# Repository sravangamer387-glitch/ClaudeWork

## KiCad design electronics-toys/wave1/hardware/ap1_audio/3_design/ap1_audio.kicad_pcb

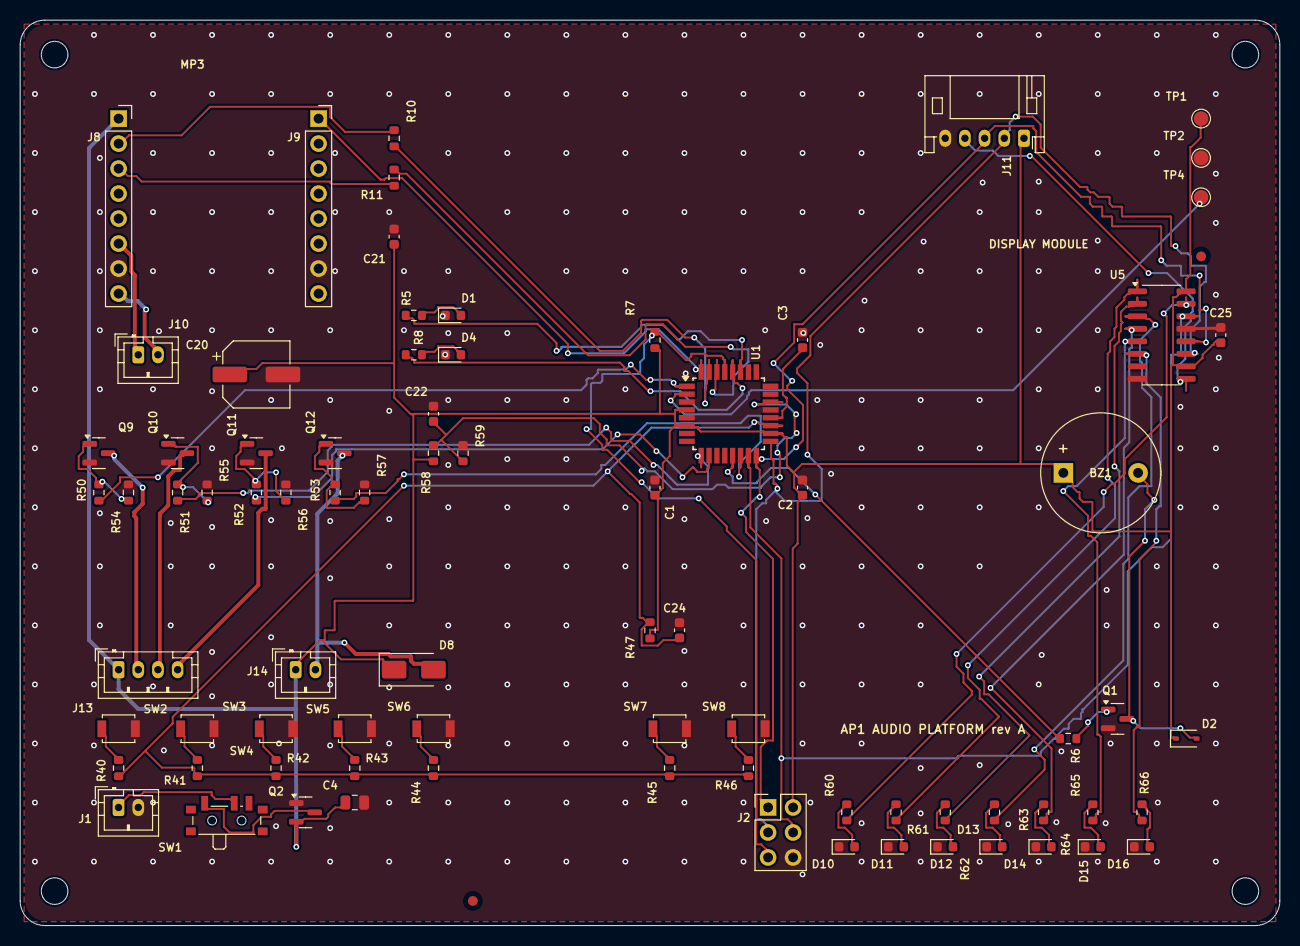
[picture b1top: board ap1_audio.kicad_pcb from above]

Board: 2 copper layers, 128.0 x 92.0 mm, 85 parts (0 on the bottom side), 60 nets.

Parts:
BZ1: Buzzer; Buzzer_12x9.5RM7.6
C1, C2, C3, C21, C22, C24, C25: 100n; C_0603_1608Metric
C4: 10u; C_0805_2012Metric
C20: 100u/35V; CP_Elec_6.3x7.7
D1: Green; LED_0603_1608Metric
D2: 1N4148WS; D_SOD-323
D4: Amber; LED_0603_1608Metric
D8: SS14; D_SMA
D10, D11, D12, D13, D14, D15, D16: Red; LED_0603_1608Metric
FID1, FID2: Fiducial; Fiducial_1mm_Mask2mm
H1, H2, H3, H4: M2.5; MountingHole_2.7mm_M2.5
J1: BATT 3xAA; JST_PH_B2B-PH-K_1x02_P2.00mm_Vertical
J2: ISP; PinHeader_2x03_P2.54mm_Vertical
J8: MP3 module left row (VCC RX TX DACR DACL SPK1 GND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; PinSocket_1x08_P2.54mm_Vertical
J9: MP3 module right row (BUSY .. GND IO1); PinSocket_1x08_P2.54mm_Vertical
J10: Speaker 3 W 4-8 ohm; JST_PH_B2B-PH-K_1x02_P2.00mm_Vertical
J11: Display module (VCC SCLK RCLK DIO GND); JST_PH_S5B-PH-K_1x05_P2.00mm_Horizontal
J13: RGB LED (common anode) / lamp; JST_PH_B4B-PH-K_1x04_P2.00mm_Vertical
J14: Projector motor; JST_PH_B2B-PH-K_1x02_P2.00mm_Vertical
Q1: MMBT3904; SOT-23
Q2: AO3401A; SOT-23
Q9, Q10, Q11, Q12: AO3400A; SOT-23
R5, R6, R8, R10, R11, R40, R60, R61, R62, R63, R64, R65, R66: 1k; R_0603_1608Metric
R7, R47: 10k; R_0603_1608Metric
R41: 2.2k; R_0603_1608Metric
R42: 3.9k; R_0603_1608Metric
R43: 6.8k; R_0603_1608Metric
R44: 12k; R_0603_1608Metric
R45: 22k; R_0603_1608Metric
R46: 47k; R_0603_1608Metric
R50, R51, R52, R53: 100; R_0603_1608Metric
R54, R55, R56, R57, R58, R59: 100k; R_0603_1608Metric
SW1: Power; SW_SPDT_PCM12
SW2: Button 1; SW_SPST_B3U-1000P
SW3: Button 2; SW_SPST_B3U-1000P
SW4: Button 3; SW_SPST_B3U-1000P
SW5: Button 4; SW_SPST_B3U-1000P
SW6: Button 5; SW_SPST_B3U-1000P
SW7: Button 6; SW_SPST_B3U-1000P
SW8: Button 7; SW_SPST_B3U-1000P
TP1, TP2, TP4: TP; TestPoint_Pad_D1.5mm
U1: ATmega328P-AU; TQFP-32_7x7mm_P0.8mm
U5: 74HC595; SOIC-16_3.9x9.9mm_P1.27mm

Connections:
+4V5: BZ1.1, C1.1, C2.1, C4.1, C20.1, C21.1, C25.1, D2.1, D8.1, J2.2, J8.1, J11.1, J13.1, J14.1, Q2.2, R7.1, R47.1, R58.1, TP1.1, U1.4, U1.6, U1.18, U5.10, U5.16
AREF: C3.1, U1.20
BAT_P: J1.1, SW1.2
BAT_SW: Q2.3, SW1.1
BTN0_N: R40.2, SW2.1
BTN1_N: R41.2, SW3.1
BTN2_N: R42.2, SW4.1
BTN3_N: R43.2, SW5.1
BTN4_N: R44.2, SW6.1
BTN5_N: R45.2, SW7.1
BTN6_N: R46.2, SW8.1
BTN_ADC: C24.1, R40.1, R41.1, R42.1, R43.1, R44.1, R45.1, R46.1, R47.2, U1.19
BUZ: R6.1, U1.13
BUZ_B: Q1.1, R6.2
BZ_N: BZ1.2, D2.2, Q1.3
B_G: Q11.1, R52.2, R56.1
B_K: J13.4, Q11.3
D1_A: D1.2, R5.2
D4_A: D4.2, R8.2
DISP_DIO: J11.4, U5.9
GND: C1.2, C2.2, C3.2, C4.2, C20.2, C21.2, C22.2, C24.2, C25.2, D1.1, D4.1, D10.1, D11.1, D12.1, D13.1, D14.1, D15.1, D16.1, J1.2, J2.6, J8.7, J9.7, J11.5, Q1.2, Q2.1, Q9.2, Q10.2, Q11.2, Q12.2, R54.2, R55.2, R56.2, R57.2, R59.2, SW2.2, SW3.2, SW4.2, SW5.2, SW6.2, SW7.2, SW8.2, TP2.1, U1.3, U1.5, U1.21, U5.8, U5.13
G_G: Q10.1, R51.2, R55.1
G_K: J13.3, Q10.3
LANE0: R60.1, U5.15
LANE0_A: D10.2, R60.2
LANE1: R61.1, U5.1
LANE1_A: D11.2, R61.2
LANE2: R62.1, U5.2
LANE2_A: D12.2, R62.2
LANE3: R63.1, U5.3
LANE3_A: D13.2, R63.2
LANE4: R64.1, U5.4
LANE4_A: D14.2, R64.2
LANE5: R65.1, U5.5
LANE5_A: D15.2, R65.2
LANE6: R66.1, U5.6
LANE6_A: D16.2, R66.2
LED_PLAY: R5.1, U1.27
LED_SLEEP: R8.1, U1.28
MISO: J2.1, J11.3, U1.16, U5.12
MOSI: J2.4, U1.15, U5.14
MOTOR: R53.1, U1.14
MOT_N: D8.2, J14.2, Q12.3
MP3_BUSY: J9.1, U1.32
MP3_RX: J8.2, R10.2
MP3_TX: J8.3, R11.1
M_G: Q12.1, R53.2, R57.1
PWM_B: R52.1, U1.10
PWM_G: R51.1, U1.9
PWM_R: R50.1, U1.1
RESET: J2.5, R7.2, U1.29
RXD: R11.2, U1.30
R_G: Q9.1, R50.2, R54.1
R_K: J13.2, Q9.3
SCK: J2.3, J11.2, U1.17, U5.11
SPK1: J8.6, J10.1
SPK2: J8.8, J10.2
TEST: TP4.1, U1.2
TXD: R10.1, U1.31
VBAT_ADC: C22.1, R58.2, R59.1, U1.22

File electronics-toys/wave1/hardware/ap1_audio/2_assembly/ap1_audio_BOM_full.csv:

Ref,Value,Footprint,Manufacturer part,LCSC #,LCSC status,Assembly
U1,ATmega328P-AU,Package_QFP:TQFP-32_7x7mm_P0.8mm,ATMEGA328P-AU,C14877,verified,SMT (JLC)
C1,100n,Capacitor_SMD:C_0603_1608Metric,Samsung CL10B104KB8NNNC 0603 100nF X7R 50V,C1591,verified,SMT (JLC)
C2,100n,Capacitor_SMD:C_0603_1608Metric,Samsung CL10B104KB8NNNC 0603 100nF X7R 50V,C1591,verified,SMT (JLC)
C3,100n,Capacitor_SMD:C_0603_1608Metric,Samsung CL10B104KB8NNNC 0603 100nF X7R 50V,C1591,verified,SMT (JLC)
R7,10k,Resistor_SMD:R_0603_1608Metric,0603 10k 1%,C25804,verified,SMT (JLC)
J2,ISP,Connector_PinHeader_2.54mm:PinHeader_2x03_P2.54mm_Vertical,HCTL PZ254-2-03-Z-8.5 (ZHOURI C5116479 had only 340 in stock),C2894964,verified,hand/THT
J1,BATT 3xAA,Connector_JST:JST_PH_B2B-PH-K_1x02_P2.00mm_Vertical,JST B2B-PH-K-S(LF)(SN),C131337,verified,hand/THT
SW1,Power,Button_Switch_SMD:SW_SPDT_PCM12,C&K PCM12SMTR,C221841,verified,SMT (JLC)
Q2,AO3401A,Package_TO_SOT_SMD:SOT-23,AO3401A,C15127,verified,SMT (JLC)
C4,10u,Capacitor_SMD:C_0805_2012Metric,0805 10uF X5R,C15850,verified,SMT (JLC)
BZ1,Buzzer,Buzzer_Beeper:Buzzer_12x9.5RM7.6,YUEXIN KC1206 16 ohm passive magnetic 12x9.5 mm (2048 Hz),C781869,verified,hand/THT
Q1,MMBT3904,Package_TO_SOT_SMD:SOT-23,MMBT3904,C20526,verified,SMT (JLC)
D2,1N4148WS,Diode_SMD:D_SOD-323,1N4148WS,C2128,verified,SMT (JLC)
R6,1k,Resistor_SMD:R_0603_1608Metric,0603 1k 1%,C21190,verified,SMT (JLC)
D1,Green,LED_SMD:LED_0603_1608Metric,"Hubei KENTO KT-0603YG yellow-green 570 nm, Vf about 2 V (lights well from 3.3 V with 1 k; the Everlight 19-217 green was out of stock)",C2289,verified,SMT (JLC)
R5,1k,Resistor_SMD:R_0603_1608Metric,0603 1k 1%,C21190,verified,SMT (JLC)
D4,Amber,LED_SMD:LED_0603_1608Metric,Hubei KENTO KT-0603Y yellow (Everlight 19-213 was out of stock),C2287,verified,SMT (JLC)
R8,1k,Resistor_SMD:R_0603_1608Metric,0603 1k 1%,C21190,verified,SMT (JLC)
J8,MP3 module left row (VCC RX TX DACR DACL SPK1 GND SPK2),Connector_PinSocket_2.54mm:PinSocket_1x08_P2.54mm_Vertical,hanxia HX PM2.54-1x8P ZC-Y,C22438158,verified,hand/THT
J9,MP3 module right row (BUSY .. GND IO1),Connector_PinSocket_2.54mm:PinSocket_1x08_P2.54mm_Vertical,hanxia HX PM2.54-1x8P ZC-Y,C22438158,verified,hand/THT
R10,1k,Resistor_SMD:R_0603_1608Metric,0603 1k 1%,C21190,verified,SMT (JLC)
R11,1k,Resistor_SMD:R_0603_1608Metric,0603 1k 1%,C21190,verified,SMT (JLC)
C21,100n,Capacitor_SMD:C_0603_1608Metric,Samsung CL10B104KB8NNNC 0603 100nF X7R 50V,C1591,verified,SMT (JLC)
C20,100u/35V,Capacitor_SMD:CP_Elec_6.3x7.7,Lelon VZH101M1VTR-0607,C176683,verified,SMT (JLC)
J10,Speaker 3 W 4-8 ohm,Connector_JST:JST_PH_B2B-PH-K_1x02_P2.00mm_Vertical,JST B2B-PH-K-S(LF)(SN),C131337,verified,hand/THT
J11,Display module (VCC SCLK RCLK DIO GND),Connector_JST:JST_PH_S5B-PH-K_1x05_P2.00mm_Horizontal,JST S5B-PH-K-S(LF)(SN),C157923,verified,hand/THT
U5,74HC595,Package_SO:SOIC-16_3.9x9.9mm_P1.27mm,74HC595D,C5947,verified,SMT (JLC)
C25,100n,Capacitor_SMD:C_0603_1608Metric,Samsung CL10B104KB8NNNC 0603 100nF X7R 50V,C1591,verified,SMT (JLC)
R60,1k,Resistor_SMD:R_0603_1608Metric,0603 1k 1%,C21190,verified,SMT (JLC)
R61,1k,Resistor_SMD:R_0603_1608Metric,0603 1k 1%,C21190,verified,SMT (JLC)
R62,1k,Resistor_SMD:R_0603_1608Metric,0603 1k 1%,C21190,verified,SMT (JLC)
R63,1k,Resistor_SMD:R_0603_1608Metric,0603 1k 1%,C21190,verified,SMT (JLC)
R64,1k,Resistor_SMD:R_0603_1608Metric,0603 1k 1%,C21190,verified,SMT (JLC)
R65,1k,Resistor_SMD:R_0603_1608Metric,0603 1k 1%,C21190,verified,SMT (JLC)
R66,1k,Resistor_SMD:R_0603_1608Metric,0603 1k 1%,C21190,verified,SMT (JLC)
D10,Red,LED_SMD:LED_0603_1608Metric,Hubei KENTO KT-0603R red (Everlight 19-217 was out of stock),C2286,verified,SMT (JLC)
D11,Red,LED_SMD:LED_0603_1608Metric,Hubei KENTO KT-0603R red (Everlight 19-217 was out of stock),C2286,verified,SMT (JLC)
D12,Red,LED_SMD:LED_0603_1608Metric,Hubei KENTO KT-0603R red (Everlight 19-217 was out of stock),C2286,verified,SMT (JLC)
D13,Red,LED_SMD:LED_0603_1608Metric,Hubei KENTO KT-0603R red (Everlight 19-217 was out of stock),C2286,verified,SMT (JLC)
D14,Red,LED_SMD:LED_0603_1608Metric,Hubei KENTO KT-0603R red (Everlight 19-217 was out of stock),C2286,verified,SMT (JLC)
D15,Red,LED_SMD:LED_0603_1608Metric,Hubei KENTO KT-0603R red (Everlight 19-217 was out of stock),C2286,verified,SMT (JLC)
D16,Red,LED_SMD:LED_0603_1608Metric,Hubei KENTO KT-0603R red (Everlight 19-217 was out of stock),C2286,verified,SMT (JLC)
SW2,Button 1,Button_Switch_SMD:SW_SPST_B3U-1000P,Omron B3U-1000P,C231329,verified,SMT (JLC)
SW3,Button 2,Button_Switch_SMD:SW_SPST_B3U-1000P,Omron B3U-1000P,C231329,verified,SMT (JLC)
SW4,Button 3,Button_Switch_SMD:SW_SPST_B3U-1000P,Omron B3U-1000P,C231329,verified,SMT (JLC)
SW5,Button 4,Button_Switch_SMD:SW_SPST_B3U-1000P,Omron B3U-1000P,C231329,verified,SMT (JLC)
SW6,Button 5,Button_Switch_SMD:SW_SPST_B3U-1000P,Omron B3U-1000P,C231329,verified,SMT (JLC)
SW7,Button 6,Button_Switch_SMD:SW_SPST_B3U-1000P,Omron B3U-1000P,C231329,verified,SMT (JLC)
SW8,Button 7,Button_Switch_SMD:SW_SPST_B3U-1000P,Omron B3U-1000P,C231329,verified,SMT (JLC)
R40,1k,Resistor_SMD:R_0603_1608Metric,UNI-ROYAL 0603WAF1001T5E,C21190,verified,SMT (JLC)
R41,2.2k,Resistor_SMD:R_0603_1608Metric,UNI-ROYAL 0603WAF2201T5E,C4190,verified,SMT (JLC)
R42,3.9k,Resistor_SMD:R_0603_1608Metric,UNI-ROYAL 0603WAF3901T5E,C23018,verified,SMT (JLC)
R43,6.8k,Resistor_SMD:R_0603_1608Metric,UNI-ROYAL 0603WAF6801T5E,C23212,verified,SMT (JLC)
R44,12k,Resistor_SMD:R_0603_1608Metric,UNI-ROYAL 0603WAF1202T5E,C22790,verified,SMT (JLC)
R45,22k,Resistor_SMD:R_0603_1608Metric,UNI-ROYAL 0603WAF2202T5E,C31850,verified,SMT (JLC)
R46,47k,Resistor_SMD:R_0603_1608Metric,UNI-ROYAL 0603WAF4702T5E,C25819,verified,SMT (JLC)
R47,10k,Resistor_SMD:R_0603_1608Metric,0603 10k 1%,C25804,verified,SMT (JLC)
C24,100n,Capacitor_SMD:C_0603_1608Metric,Samsung CL10B104KB8NNNC 0603 100nF X7R 50V,C1591,verified,SMT (JLC)
Q9,AO3400A,Package_TO_SOT_SMD:SOT-23,AO3400A,C20917,verified,SMT (JLC)
Q10,AO3400A,Package_TO_SOT_SMD:SOT-23,AO3400A,C20917,verified,SMT (JLC)
Q11,AO3400A,Package_TO_SOT_SMD:SOT-23,AO3400A,C20917,verified,SMT (JLC)
Q12,AO3400A,Package_TO_SOT_SMD:SOT-23,AO3400A,C20917,verified,SMT (JLC)
R50,100,Resistor_SMD:R_0603_1608Metric,UNI-ROYAL 0603WAF1000T5E,C22775,verified,SMT (JLC)
R51,100,Resistor_SMD:R_0603_1608Metric,UNI-ROYAL 0603WAF1000T5E,C22775,verified,SMT (JLC)
R52,100,Resistor_SMD:R_0603_1608Metric,UNI-ROYAL 0603WAF1000T5E,C22775,verified,SMT (JLC)
R53,100,Resistor_SMD:R_0603_1608Metric,UNI-ROYAL 0603WAF1000T5E,C22775,verified,SMT (JLC)
R54,100k,Resistor_SMD:R_0603_1608Metric,0603 100k 1%,C25803,verified,SMT (JLC)
R55,100k,Resistor_SMD:R_0603_1608Metric,0603 100k 1%,C25803,verified,SMT (JLC)
R56,100k,Resistor_SMD:R_0603_1608Metric,0603 100k 1%,C25803,verified,SMT (JLC)
R57,100k,Resistor_SMD:R_0603_1608Metric,0603 100k 1%,C25803,verified,SMT (JLC)
J13,RGB LED (common anode) / lamp,Connector_JST:JST_PH_B4B-PH-K_1x04_P2.00mm_Vertical,JST B4B-PH-K-S(LF)(SN),C131334,verified,hand/THT
J14,Projector motor,Connector_JST:JST_PH_B2B-PH-K_1x02_P2.00mm_Vertical,JST B2B-PH-K-S(LF)(SN),C131337,verified,hand/THT
D8,SS14,Diode_SMD:D_SMA,SS14,C84343,verified,SMT (JLC)
R58,100k,Resistor_SMD:R_0603_1608Metric,0603 100k 1%,C25803,verified,SMT (JLC)
R59,100k,Resistor_SMD:R_0603_1608Metric,0603 100k 1%,C25803,verified,SMT (JLC)
C22,100n,Capacitor_SMD:C_0603_1608Metric,Samsung CL10B104KB8NNNC 0603 100nF X7R 50V,C1591,verified,SMT (JLC)
TP1,TP,TestPoint:TestPoint_Pad_D1.5mm,,,,hand/THT
TP2,TP,TestPoint:TestPoint_Pad_D1.5mm,,,,hand/THT
TP4,TP,TestPoint:TestPoint_Pad_D1.5mm,,,,hand/THT

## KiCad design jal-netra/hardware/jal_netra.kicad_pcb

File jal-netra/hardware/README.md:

# Jal-Netra ultrasonic flow main board (rev A)

Jal-Netra main board: STM32G431 transit-time measurement (bridge-driven piezo, input mux, two-stage low-noise receive chain, gain select, 12-bit 4 MS/s ADC), USB-C powered, OLED/UART/SWD.

**Status: engineering release, software-verified only (ERC on the netlist, KiCad DRC, netlist cross-check, SPICE where noted). Not yet built, not reviewed by a second engineer, not certified.**

## Specification
- Board 86 x 66 mm, 2 layers, 1.6 mm FR-4, 1 oz copper, rounded corners R2.5 mm, 4 x M2.5 mounting holes, 2 fiducials.
- Rules used: min track 0.2 mm (power 0.4 mm), min clearance 0.15 mm, via 0.6/0.3 mm, GND pour on both layers, 128 stitching vias.
- Finish: ENIG recommended (HASL lead-free acceptable); green mask, white silk; IPC class 2.
- 78 parts, 51 nets.

## Circuit description
- **Transmit:** TIM3 channels on PA6/PA4 (transducer A) and PB0/PB1 (transducer B) generate a 6-cycle 1 MHz burst; the second pin of each pair is inverted for bridge drive (6.6 Vpp). 22 ohm series resistors protect the pins; on receive one leg is held low by its timer pin and the other is high-impedance.
- **Receive:** 10 nF + 1 k tap from the transducer's high leg, BAV99 clamp to the rails, TS5A3159 selects transducer A or B into LNA1 (OPA356, x10.2) and LNA2 (x10.2); TS5A3159 U7 selects 20 dB or 40 dB into a 33 ohm / 22 pF filter and ADC1 (PA0). Mid-supply bias 1.65 V from AVDD (ferrite-filtered 3.3 V).
- **Rest:** STM32G431CBT6 with 8 MHz crystal, SWD header, boot0 pull-down, USB-C power-only (5.1 k CC, PTC, TVS), AP2112K-3.3, OLED and UART headers, buzzer, LED, test button, test points on the receive chain.

### Simulation: `../../jal-netra/sim/lna_results.txt`
```
SPICE (ngspice) of the receive chain, source impedance 270 ohm (piezo at 1 MHz), OPA356-class model (A0 1e5, GBW 200 MHz):
stage 1 gain at 1 MHz        = 20.1 dB (target 20 dB)
stage 1 + 2 gain at 1 MHz   = 40.9 dB (target 40 dB)
stage 1 upper -3 dB          = 20 MHz
stage 1 + 2 band (-3 dB)      = 1.5 kHz ... 14 MHz
```

## Power
MCU 170 MHz about 35 mA while measuring (0.5 s per measurement), LNAs 2 x 8 mA: USB powered only (about 0.1 W average with a 10 s idle period).

## Verification
| Check | Result |
|---|---|
| Electrical rule check on the netlist (own ERC: unconnected pins, single-pin nets, output conflicts, unpowered supplies, symbol/footprint pin match) | 0 errors, 0 warnings |
| KiCad DRC | 0 errors, 0 warnings; unconnected pads: 0 |
| Schematic netlist equals PCB netlist | yes |
| Router failures | 0 |
| 3D STEP export | yes |
| Independent Gerber parse (gerbonara): layers parsed, outline size equals the design | 9 layers, outline [86.1, 66.1] mm, match |

Enclosure (prototype shell for 3D printing): outer 101.2 x 81.2 x 22.0 mm, collision/opening check: pass

## Bill of materials
| Ref | Value | Footprint | Manufacturer part | LCSC # | LCSC status |
|---|---|---|---|---|---|
| U1 | STM32G431CBT6 | LQFP-48_7x7mm_P0.5mm | STM32G431CBT6 (LQFP-48) | C529355 | verified |
| U4 | TS5A3159 | SOT-363_SC-70-6 | TI TS5A3159DCKR | C46388 | verified |
| U5 | OPA356 | SOT-23-5 | TI OPA356AIDBVR | C183100 | verified |
| U6 | OPA356 | SOT-23-5 | TI OPA356AIDBVR | C183100 | verified |
| U7 | TS5A3159 | SOT-363_SC-70-6 | TI TS5A3159DCKR | C46388 | verified |
| U3 | AP2112K-3.3 | SOT-23-5 | Diodes AP2112K-3.3TRG1 (from the LCSC datasheet link) | C51118 | verified |
| FB1 | BLM18 600R | L_0603_1608Metric | Murata BLM18AG601SN1D | C19330 | verified |
| Y1 | 8 MHz | Crystal_SMD_3225-4Pin_3.2x2.5mm | YXC X32258MOB4SI 8 MHz 12 pF 3225 (matches the 15 pF load caps) | C2682775 | verified |
| D5 | BAV99 | SOT-23 | JSCJ BAV99 | C68983 | verified |
| D6 | BAV99 | SOT-23 | JSCJ BAV99 | C68983 | verified |
| J6 | Transducer A (BTL) | JST_PH_B2B-PH-K_1x02_P2.00mm_Vertical | JST B2B-PH-K-S(LF)(SN) | C131337 | verified |
| J7 | Transducer B (BTL) | JST_PH_B2B-PH-K_1x02_P2.00mm_Vertical | JST B2B-PH-K-S(LF)(SN) | C131337 | verified |
| R30 | 22 | R_0603_1608Metric | UNI-ROYAL 0603WAF220JT5E | C23345 | verified |
| R31 | 22 | R_0603_1608Metric | UNI-ROYAL 0603WAF220JT5E | C23345 | verified |
| R32 | 22 | R_0603_1608Metric | UNI-ROYAL 0603WAF220JT5E | C23345 | verified |
| R33 | 22 | R_0603_1608Metric | UNI-ROYAL 0603WAF220JT5E | C23345 | verified |
| C20 | 10n | C_0603_1608Metric | Samsung CL10B103KB8NNNC 0603 10nF X7R 50V | C1589 | verified |
| R35 | 1k | R_0603_1608Metric | 0603 1k 1% | C21190 | verified |
| C21 | 10n | C_0603_1608Metric | Samsung CL10B103KB8NNNC 0603 10nF X7R 50V | C1589 | verified |
| R36 | 1k | R_0603_1608Metric | 0603 1k 1% | C21190 | verified |
| C22 | 100n | C_0603_1608Metric | Samsung CL10B104KB8NNNC 0603 100nF X7R 50V | C1591 | verified |
| C23 | 100n | C_0603_1608Metric | Samsung CL10B104KB8NNNC 0603 100nF X7R 50V | C1591 | verified |
| C24 | 100n | C_0603_1608Metric | Samsung CL10B104KB8NNNC 0603 100nF X7R 50V | C1591 | verified |
| C25 | 1u | C_0603_1608Metric | 0603 1uF X7R | C15849 | verified |
| R10 | 10k | R_0603_1608Metric | 0603 10k 1% | C25804 | verified |
| R11 | 10k | R_0603_1608Metric | 0603 10k 1% | C25804 | verified |
| C27 | 1u | C_0603_1608Metric | 0603 1uF X7R | C15849 | verified |
| C28 | 10n | C_0603_1608Metric | Samsung CL10B103KB8NNNC 0603 10nF X7R 50V | C1589 | verified |
| R12 | 100k | R_0603_1608Metric | 0603 100k 1% | C25803 | verified |
| R13 | 2.2k | R_0603_1608Metric | 0603 2.2k 1% | C4190 | verified |
| R14 | 240 | R_0603_1608Metric | UNI-ROYAL 0603WAF2400T5E (JLCPCB listing) | C23350 | verified |
| C29 | 1u | C_0603_1608Metric | 0603 1uF X7R | C15849 | verified |
| R15 | 0 | R_0603_1608Metric | UNI-ROYAL 0603WAF0000T5E | C21189 | verified |
| C30 | 10n | C_0603_1608Metric | Samsung CL10B103KB8NNNC 0603 10nF X7R 50V | C1589 | verified |
| R16 | 100k | R_0603_1608Metric | 0603 100k 1% | C25803 | verified |
| R17 | 1k | R_0603_1608Metric | 0603 1k 1% | C21190 | verified |
| R18 | 100 | R_0603_1608Metric | UNI-ROYAL 0603WAF1000T5E | C22775 | verified |
| C31 | 1u | C_0603_1608Metric | 0603 1uF X7R | C15849 | verified |
| R19 | 0 | R_0603_1608Metric | UNI-ROYAL 0603WAF0000T5E | C21189 | verified |
| R20 | 33 | R_0603_1608Metric | UNI-ROYAL 0603WAF330JT5E | C23140 | verified |
| C32 | 22p | C_0603_1608Metric | Samsung CL10C220JB8NNNC C0G | C1653 | verified |
| C1 | 100n | C_0603_1608Metric | Samsung CL10B104KB8NNNC 0603 100nF X7R 50V | C1591 | verified |
| C2 | 100n | C_0603_1608Metric | Samsung CL10B104KB8NNNC 0603 100nF X7R 50V | C1591 | verified |
| C3 | 100n | C_0603_1608Metric | Samsung CL10B104KB8NNNC 0603 100nF X7R 50V | C1591 | verified |
| C4 | 100n | C_0603_1608Metric | Samsung CL10B104KB8NNNC 0603 100nF X7R 50V | C1591 | verified |
| C33 | 100n | C_0603_1608Metric | Samsung CL10B104KB8NNNC 0603 100nF X7R 50V | C1591 | verified |
| C34 | 4.7u | C_0603_1608Metric | Samsung CL10A475KP8NNNC X5R 10V | C1705 | verified |
| C35 | 15p | C_0603_1608Metric | Samsung CL10C150JB8NNNC C0G | C1644 | verified |
| C36 | 15p | C_0603_1608Metric | Samsung CL10C150JB8NNNC C0G | C1644 | verified |
| R21 | 10k | R_0603_1608Metric | 0603 10k 1% | C25804 | verified |
| R22 | 10k | R_0603_1608Metric | 0603 10k 1% | C25804 | verified |
| C37 | 100n | C_0603_1608Metric | Samsung CL10B104KB8NNNC 0603 100nF X7R 50V | C1591 | verified |
| C38 | 1u | C_0603_1608Metric | 0603 1uF X7R | C15849 | verified |
| C39 | 1u | C_0603_1608Metric | 0603 1uF X7R | C15849 | verified |
| J4 | OLED I2C | JST_PH_B4B-PH-K_1x04_P2.00mm_Vertical | JST B4B-PH-K-S(LF)(SN) | C131334 | verified |
| R23 | 4.7k | R_0603_1608Metric | 0603 4.7k 1% | C23162 | verified |
| R24 | 4.7k | R_0603_1608Metric | 0603 4.7k 1% | C23162 | verified |
| J5 | UART host / BLE | JST_PH_B4B-PH-K_1x04_P2.00mm_Vertical | JST B4B-PH-K-S(LF)(SN) | C131334 | verified |
| J3 | SWD | PinHeader_2x03_P2.54mm_Vertical | HCTL PZ254-2-03-Z-8.5 (ZHOURI C5116479 had only 340 in stock) | C2894964 | verified |
| SW2 | Test / zero | SW_SPST_B3U-1000P | Omron B3U-1000P | C231329 | verified |
| TP1 | TP | TestPoint_Pad_D1.5mm |  |  |  |
| TP2 | TP | TestPoint_Pad_D1.5mm |  |  |  |
| TP3 | TP | TestPoint_Pad_D1.5mm |  |  |  |
| TP4 | TP | TestPoint_Pad_D1.5mm |  |  |  |
| TP5 | TP | TestPoint_Pad_D1.5mm |  |  |  |
| TP6 | TP | TestPoint_Pad_D1.5mm |  |  |  |
| J1 | USB-C 5V | USB_C_Receptacle_HRO_TYPE-C-31-M-12 | TYPE-C-31-M-12 | C165948 | verified |
| F1 | PTC 500mA | Fuse_1206_3216Metric | Littelfuse 1206L050YR (6 V) | C163512 | verified |
| D3 | SMAJ5.0A | D_SMA | Littelfuse SMAJ5.0A | C83329 | verified |
| R1 | 5.1k | R_0603_1608Metric | 0603 5.1k 1% | C23186 | verified |
| R2 | 5.1k | R_0603_1608Metric | 0603 5.1k 1% | C23186 | verified |
| C5 | 10u | C_0805_2012Metric | 0805 10uF X5R | C15850 | verified |
| BZ1 | Buzzer | Buzzer_12x9.5RM7.6 | YUEXIN KC1206 16 ohm passive magnetic 12x9.5 mm (2048 Hz) | C781869 | verified |
| Q1 | MMBT3904 | SOT-23 | MMBT3904 | C20526 | verified |
| D2 | 1N4148WS | D_SOD-323 | 1N4148WS | C2128 | verified |
| R7 | 1k | R_0603_1608Metric | 0603 1k 1% | C21190 | verified |
| D1 | Green | LED_0603_1608Metric | Hubei KENTO KT-0603YG yellow-green 570 nm, Vf about 2 V (lights well from 3.3 V with 1 k; the Everlight 19-217 green was out of stock) | C2289 | verified |
| R5 | 1k | R_0603_1608Metric | 0603 1k 1% | C21190 | verified |

`verified` = LCSC number confirmed by web search on 2026-10-31/11-01; `memory` = from my recollection, **check on lcsc.com before ordering**; empty = no number chosen (through-hole connectors, switches, buzzer, test points: hand-assembled or chosen by the buyer). `*_JLC_BOM.csv` / `*_JLC_CPL.csv` list only the parts with an LCSC number; JLCPCB rotation corrections (CPL) must be checked in their viewer.

## Assembly notes
- Reflow (JLCPCB SMT): all SMD parts with an LCSC number. Hand-solder: JST connectors, pin headers, buzzer, switches, test points as listed in the BOM. Fiducials and mounting holes are in the Gerbers.
- Polarity: LED cathode toward GND (silk marks), electrolytic none, diode D2 cathode to +V, Q2 orientation as footprint (SOT-23 pin 1 = gate).
- Programming: ISP header J2 (pin 1 = MISO, square pad). Flash the matching image from `utility10/firmware/release/`: Seeti Counter `4MHz/seeti_prod.hex` (production firmware: timer-triggered 16 kS/s ADC, scan mode to find the real whistle frequency, battery check), Rain Alert `8MHz/rain_alert.hex`, Bijli Meter Reader `8MHz/bijli_meter.hex` (demo-grade firmware, to be hardened).

## Bring-up and test
1. USB-C 5 V: +3V3 = 3.3 V, AVDD = 3.28 V, VMID = 1.64 V.
2. Flash over SWD; with the spool dry nothing should be received (amplitude near zero); fill with water: a burst of amplitude A appears at ADC_IN 40.5 us after the transmit edge (TP5).
3. Follow `jal-netra/docs/TEST_PLAN.md` gates 1-3.

## Files
`1_fabrication/` Gerber + drill zip (upload to JLCPCB/any fab), fab notes, copper plot
`2_assembly/` JLC BOM + CPL (SMD parts JLC assembles), full BOM with LCSC numbers for every part, pick-and-place, assembly drawing
`3_design/` KiCad 7 project (pcb, schematic, libs), netlist, STEP model, schematic PDF, renders
`4_enclosure/` printable enclosure (base, screwed lid, battery door, plungers / light pipes / switch extensions) or a mounting plate for a bought IP65 box; dimensions and notes in enclosure.json
`5_verification/` DRC, ERC, verification and readiness reports

## Known limits and review checklist
- Layout was produced by a custom router and software placement; a human layout review (analog routing, ground returns, creepage, connector mechanics, silkscreen) is still required.
- Not verified: EMC, ESD (apart from TVS parts where fitted), thermal, real component tolerances, supplier stock/price, assembly house design-for-manufacture check (run JLCPCB's DFM check on the Gerbers).
- Firmware thresholds are placeholders to be calibrated on prototypes.

## Manufacturing readiness (automatic check)

| Check | Result |
|---|---|
| gerber layers and drill present | PASS |
| drc errors 0 | PASS |
| unconnected 0 | PASS |
| netlist matches schematic | PASS |
| erc errors 0 | PASS |
| independent gerber check clean | PASS |
| every part has lcsc number | PASS |
| every lcsc number verified | PASS |
| cpl rows equal jlc bom parts | PASS |
| step model | PASS |
| KiCad DRC warnings | 0 |
| **Order ready** | **YES** |

Order steps: (1) upload `1_fabrication/*_gerbers.zip`; (2) for assembly upload `2_assembly/*_JLC_BOM.csv` and `*_JLC_CPL.csv`, check the 3D/rotation preview for every polarised part (diodes, ICs, LEDs, electrolytics) because CPL rotations are generated, not hand-checked; (3) buy the through-hole parts listed in `*_BOM_full.csv` marked hand/THT and solder them; (4) re-check stock and the exact LCSC listing for every line before paying.

Limits: the layout is software-generated and has not been reviewed by a PCB engineer; no prototype has been built; the first batch should be treated as a prototype run (order 5 boards).

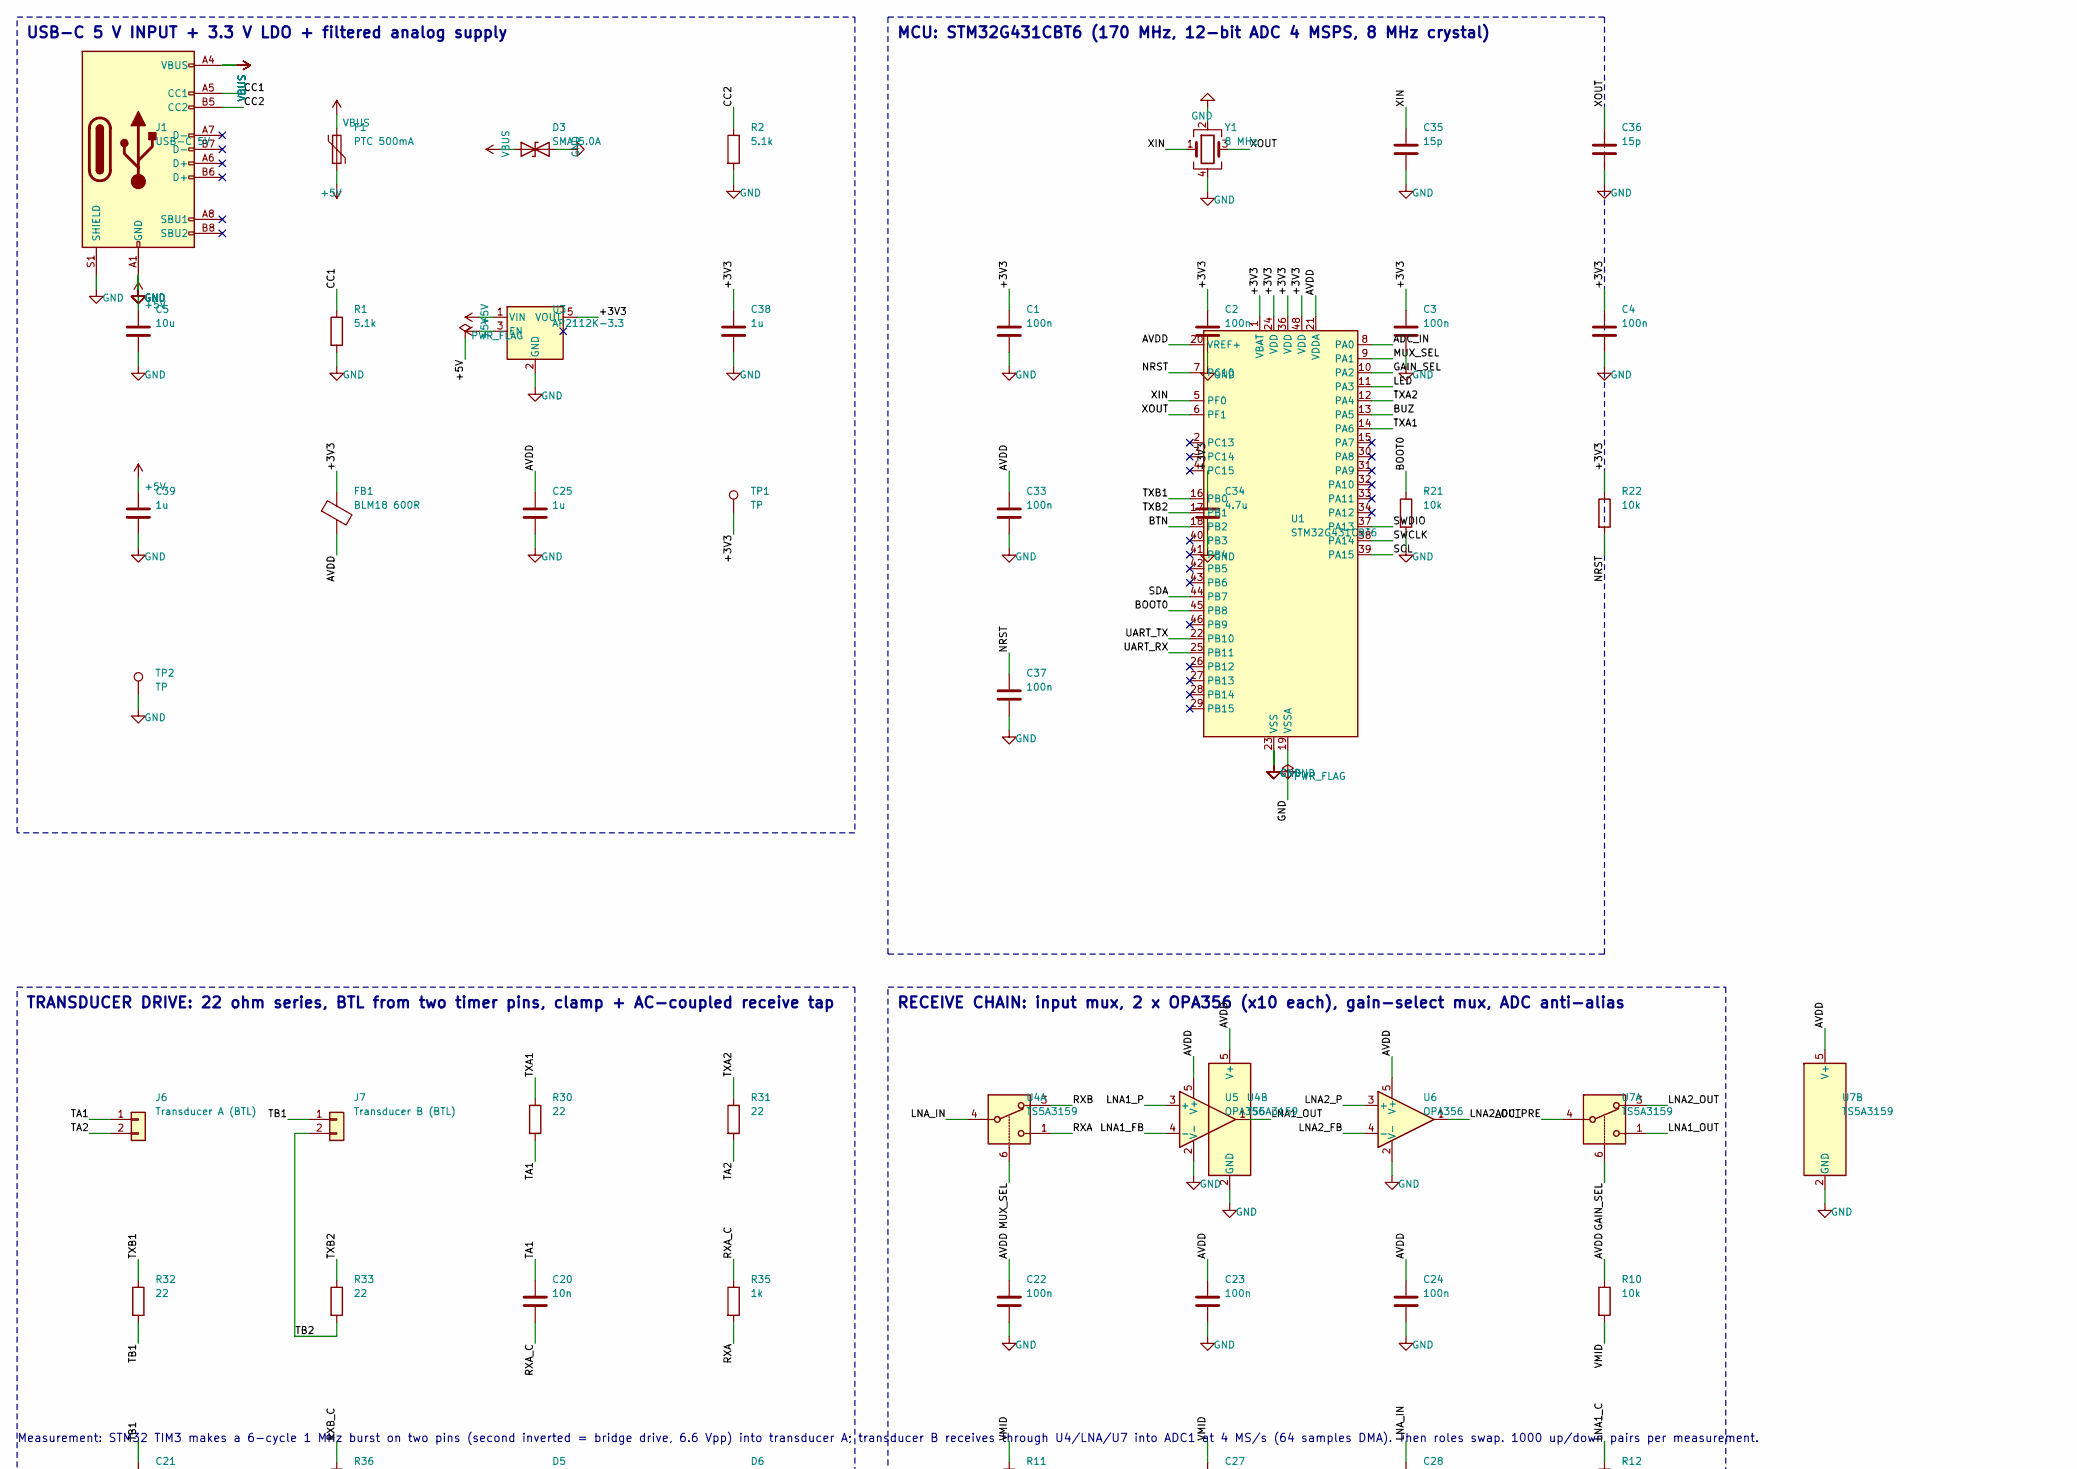
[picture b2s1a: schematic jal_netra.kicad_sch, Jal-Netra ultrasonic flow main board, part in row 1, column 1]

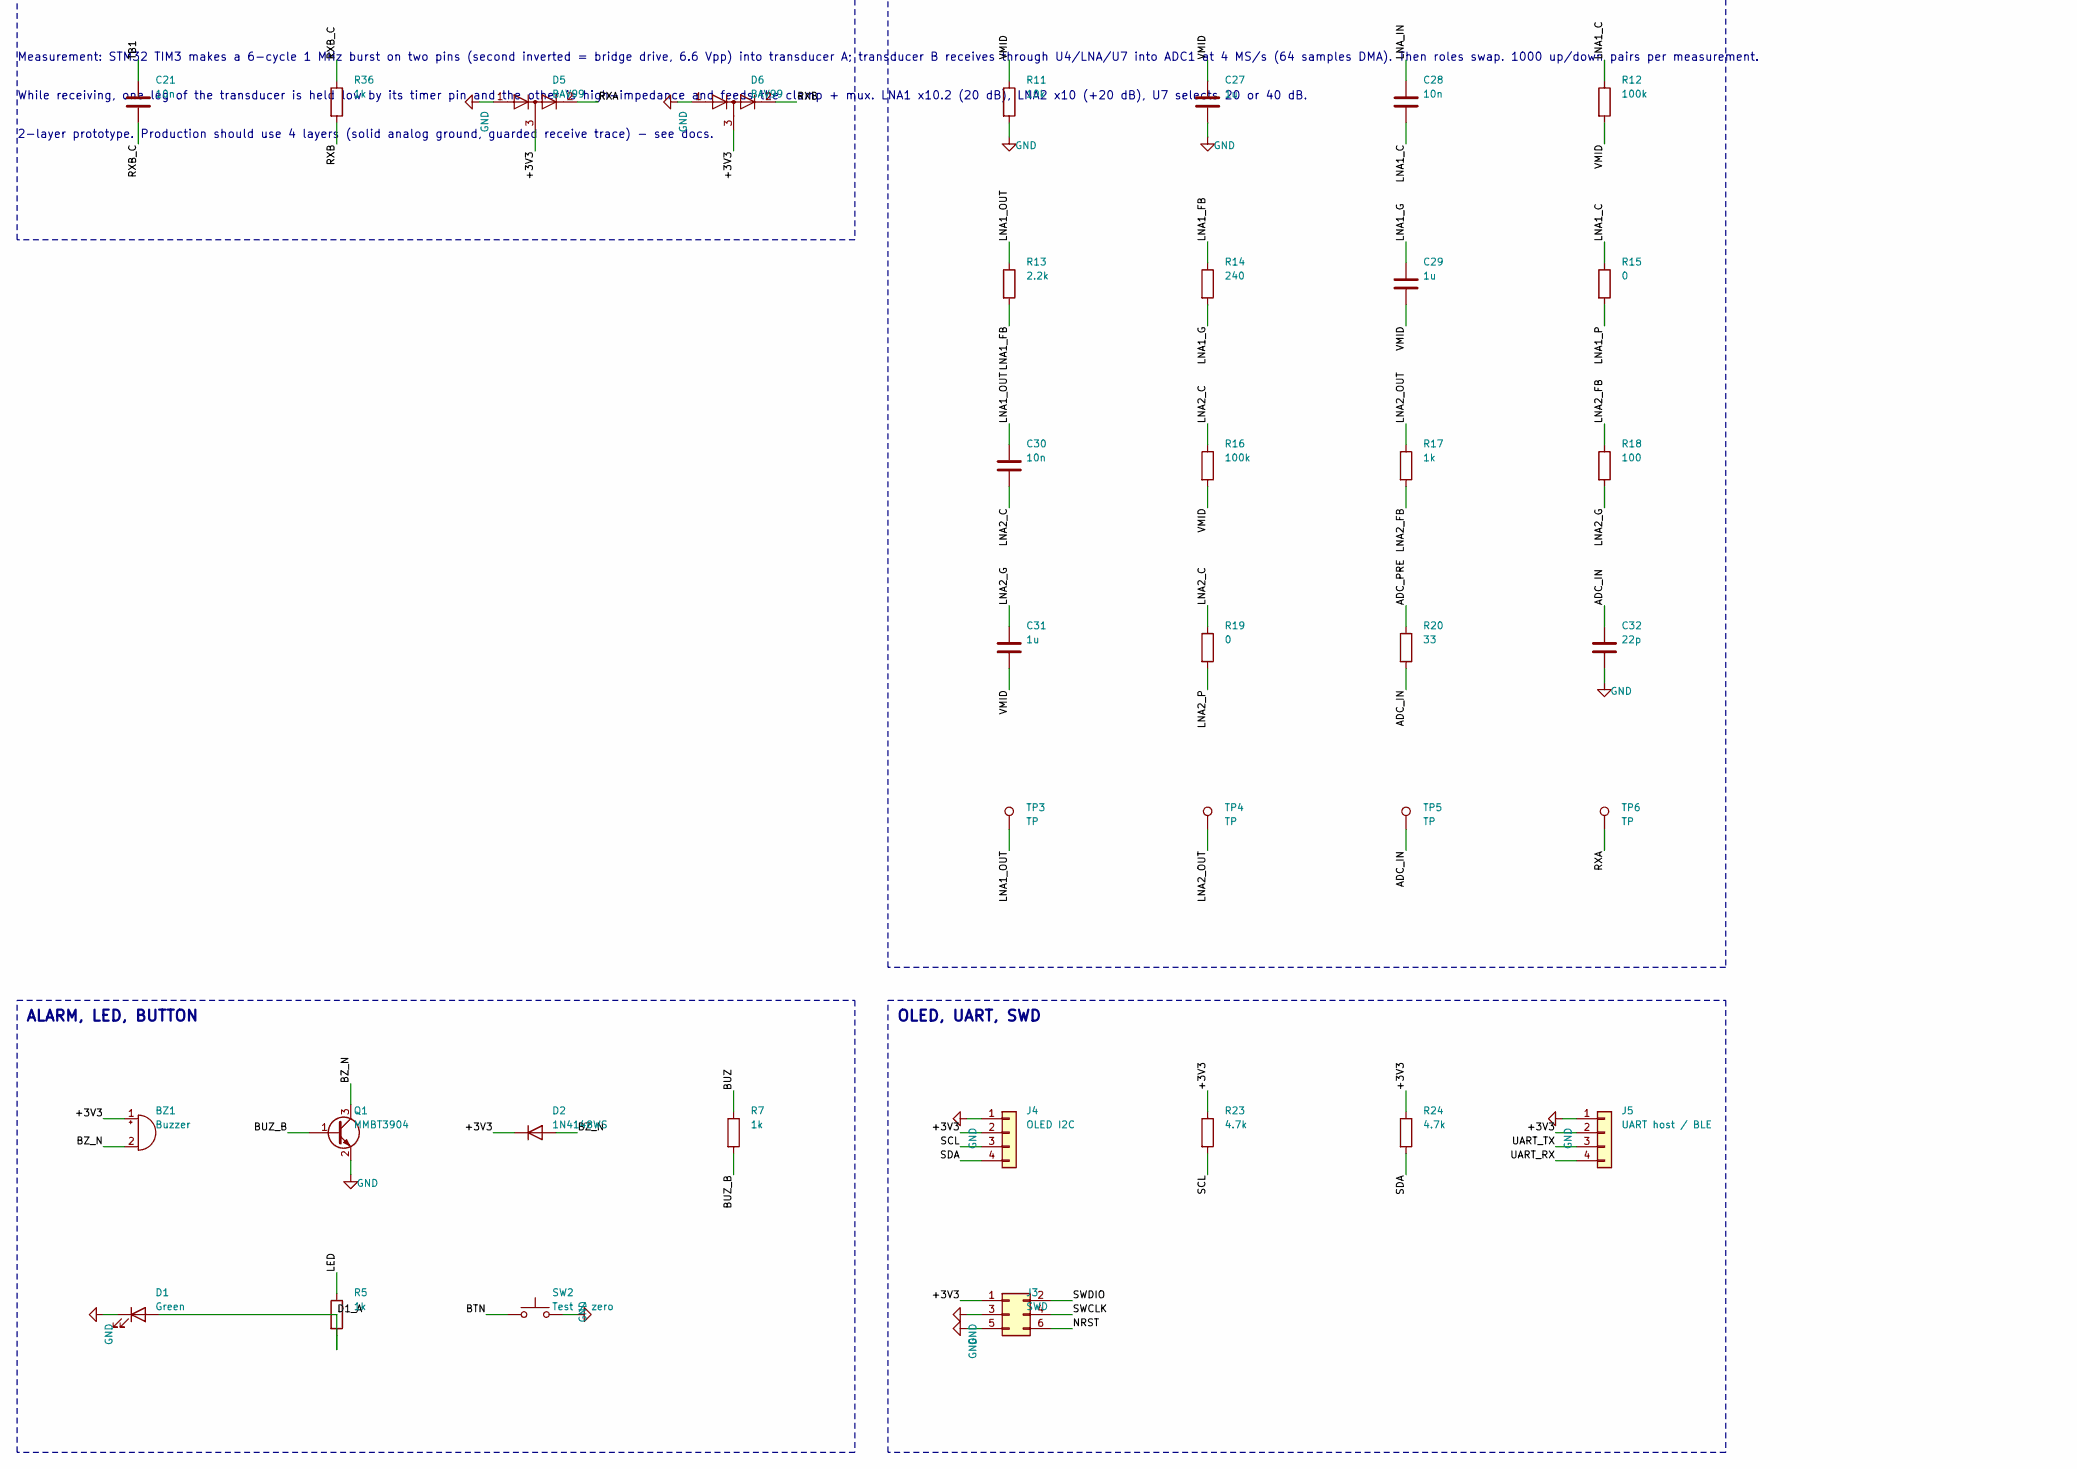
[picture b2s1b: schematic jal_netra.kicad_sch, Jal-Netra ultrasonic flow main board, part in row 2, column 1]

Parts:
BZ1: Buzzer; Buzzer_12x9.5RM7.6
C1, C2, C3, C4, C22, C23, C24, C33, C37: 100n; C_0603_1608Metric
C5: 10u; C_0805_2012Metric
C20, C21, C28, C30: 10n; C_0603_1608Metric
C25, C27, C29, C31, C38, C39: 1u; C_0603_1608Metric
C32: 22p; C_0603_1608Metric
C34: 4.7u; C_0603_1608Metric
C35, C36: 15p; C_0603_1608Metric
D1: Green; LED_0603_1608Metric
D2: 1N4148WS; D_SOD-323
D3: SMAJ5.0A; D_SMA
D5, D6: BAV99; SOT-23
F1: PTC 500mA; Fuse_1206_3216Metric
FB1: BLM18 600R; L_0603_1608Metric
J1: USB-C 5V; USB_C_Receptacle_HRO_TYPE-C-31-M-12
J3: SWD; PinHeader_2x03_P2.54mm_Vertical
J4: OLED I2C; JST_PH_B4B-PH-K_1x04_P2.00mm_Vertical
J5: UART host / BLE; JST_PH_B4B-PH-K_1x04_P2.00mm_Vertical
J6: Transducer A (BTL); JST_PH_B2B-PH-K_1x02_P2.00mm_Vertical
J7: Transducer B (BTL); JST_PH_B2B-PH-K_1x02_P2.00mm_Vertical
Q1: MMBT3904; SOT-23
R1, R2: 5.1k; R_0603_1608Metric
R5, R7, R17, R35, R36: 1k; R_0603_1608Metric
R10, R11, R21, R22: 10k; R_0603_1608Metric
R12, R16: 100k; R_0603_1608Metric
R13: 2.2k; R_0603_1608Metric
R14: 240; R_0603_1608Metric
R15, R19: 0; R_0603_1608Metric
R18: 100; R_0603_1608Metric
R20: 33; R_0603_1608Metric
R23, R24: 4.7k; R_0603_1608Metric
R30, R31, R32, R33: 22; R_0603_1608Metric
SW2: Test / zero; SW_SPST_B3U-1000P
TP1, TP2, TP3, TP4, TP5, TP6: TP; TestPoint_Pad_D1.5mm
U1: STM32G431CBT6; LQFP-48_7x7mm_P0.5mm
U3: AP2112K-3.3; SOT-23-5
U4, U7: TS5A3159; SOT-363_SC-70-6
U5, U6: OPA356; SOT-23-5
Y1: 8 MHz; Crystal_SMD_3225-4Pin_3.2x2.5mm

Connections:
+3V3: BZ1.1 (+), C1.1, C2.1, C3.1, C4.1, C34.1, C38.1, D2.1 (K), D5.3 (K), D6.3 (K), FB1.1, J3.1, J4.2, J5.2, R22.1, R23.1, R24.1, TP1.1, U1.1 (VBAT), U1.24 (VDD), U1.36 (VDD), U1.48 (VDD), U3.5 (VOUT)
+5V: C5.1, C39.1, F1.2, U3.1 (VIN), U3.3 (EN)
ADC_IN: C32.1, R20.2, TP5.1, U1.8 (PA0)
ADC_PRE: R20.1, U7.4
AVDD: C22.1, C23.1, C24.1, C25.1, C33.1, FB1.2, R10.1, U1.20 (VREF+), U1.21 (VDDA), U4.5 (V+), U5.5 (V+), U6.5 (V+), U7.5 (V+)
BOOT0: R21.1, U1.45 (PB8)
BTN: SW2.1, U1.18 (PB2)
BUZ: R7.1, U1.13 (PA5)
BUZ_B: Q1.1 (B), R7.2
BZ_N: BZ1.2 (-), D2.2 (A), Q1.3 (C)
CC1: J1.A5 (CC1), R1.1
CC2: J1.B5 (CC2), R2.1
D1_A: D1.2 (A), R5.2
GAIN_SEL: U1.10 (PA2), U7.6
GND: C1.2, C2.2, C3.2, C4.2, C5.2, C22.2, C23.2, C24.2, C25.2, C27.2, C32.2, C33.2, C34.2, C35.2, C36.2, C37.2, C38.2, C39.2, D1.1 (K), D3.2 (A2), D5.1 (K), D6.1 (K), J1.A1 (GND), J1.A12 (GND), J1.B1 (GND), J1.B12 (GND), J1.S1 (SHIELD), J3.3, J3.5, J4.1, J5.1, Q1.2 (E), R1.2, R2.2, R11.2, R21.2, SW2.2, TP2.1, U1.19 (VSSA), U1.23 (VSS), U1.35 (VSS), U1.47 (VSS), U3.2 (GND), U4.2 (GND), U5.2 (V-), U6.2 (V-), U7.2 (GND), Y1.2, Y1.4
LED: R5.1, U1.11 (PA3)
LNA1_C: C28.2, R12.1, R15.1
LNA1_FB: R13.2, R14.1, U5.4 (-)
LNA1_G: C29.1, R14.2
LNA1_OUT: C30.1, R13.1, TP3.1, U5.1, U7.1
LNA1_P: R15.2, U5.3 (+)
LNA2_C: C30.2, R16.1, R19.1
LNA2_FB: R17.2, R18.1, U6.4 (-)
LNA2_G: C31.1, R18.2
LNA2_OUT: R17.1, TP4.1, U6.1, U7.3
LNA2_P: R19.2, U6.3 (+)
LNA_IN: C28.1, U4.4
MUX_SEL: U1.9 (PA1), U4.6
NRST: C37.1, J3.6, R22.2, U1.7 (PG10)
RXA: D5.2 (A), R35.2, TP6.1, U4.1
RXA_C: C20.2, R35.1
RXB: D6.2 (A), R36.2, U4.3
RXB_C: C21.2, R36.1
SCL: J4.3, R23.2, U1.39 (PA15)
SDA: J4.4, R24.2, U1.44 (PB7)
SWCLK: J3.4, U1.38 (PA14)
SWDIO: J3.2, U1.37 (PA13)
TA1: C20.1, J6.1, R30.2
TA2: J6.2, R31.2
TB1: C21.1, J7.1, R32.2
TB2: J7.2, R33.2
TXA1: R30.1, U1.14 (PA6)
TXA2: R31.1, U1.12 (PA4)
TXB1: R32.1, U1.16 (PB0)
TXB2: R33.1, U1.17 (PB1)
UART_RX: J5.4, U1.25 (PB11)
UART_TX: J5.3, U1.22 (PB10)
VBUS: D3.1 (A1), F1.1, J1.A4 (VBUS), J1.A9 (VBUS), J1.B4 (VBUS), J1.B9 (VBUS)
VMID: C27.1, C29.2, C31.2, R10.2, R11.1, R12.2, R16.2
XIN: C35.1, U1.5 (PF0), Y1.1
XOUT: C36.1, U1.6 (PF1), Y1.3

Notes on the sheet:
USB-C 5 V INPUT + 3.3 V LDO + filtered analog supply
MCU: STM32G431CBT6 (170 MHz, 12-bit ADC 4 MSPS, 8 MHz crystal)
TRANSDUCER DRIVE: 22 ohm series, BTL from two timer pins, clamp + AC-coupled receive tap
RECEIVE CHAIN: input mux, 2 x OPA356 (x10 each), gain-select mux, ADC anti-alias
ALARM, LED, BUTTON
OLED, UART, SWD
Measurement: STM32 TIM3 makes a 6-cycle 1 MHz burst on two pins (second inverted = bridge drive, 6.6 Vpp) into transducer A; transducer B receives through U4/LNA/U7 into ADC1 at 4 MS/s (64 samples DMA). Then roles swap. 1000 up/down pairs per measurement.
While receiving, one leg of the transducer is held low by its timer pin and the other is high-impedance and feeds the clamp + mux. LNA1 x10.2 (20 dB), LNA2 x10 (+20 dB), U7 selects 20 or 40 dB.
2-layer prototype. Production should use 4 layers (solid analog ground, guarded receive trace) - see docs.
